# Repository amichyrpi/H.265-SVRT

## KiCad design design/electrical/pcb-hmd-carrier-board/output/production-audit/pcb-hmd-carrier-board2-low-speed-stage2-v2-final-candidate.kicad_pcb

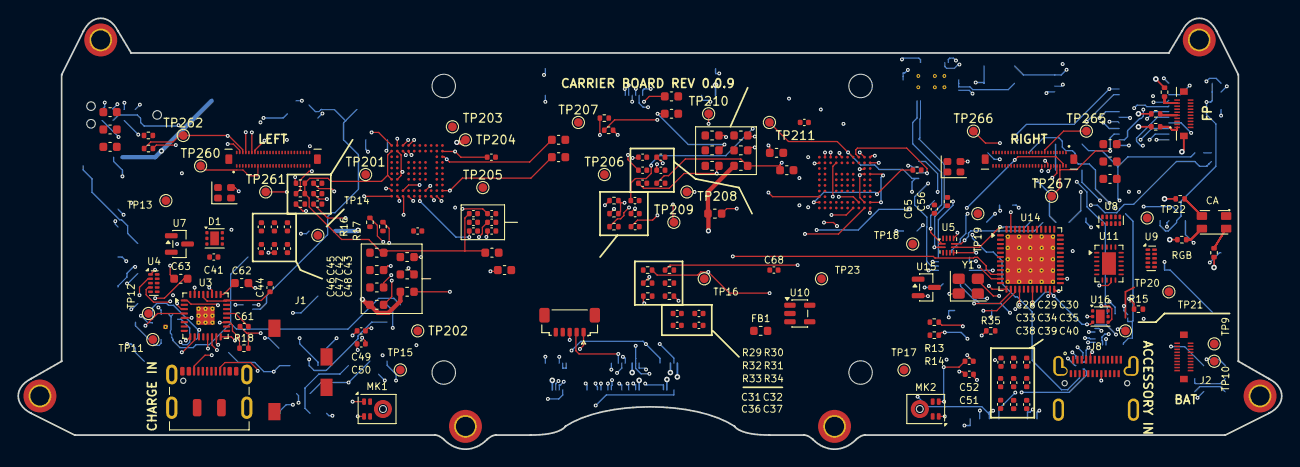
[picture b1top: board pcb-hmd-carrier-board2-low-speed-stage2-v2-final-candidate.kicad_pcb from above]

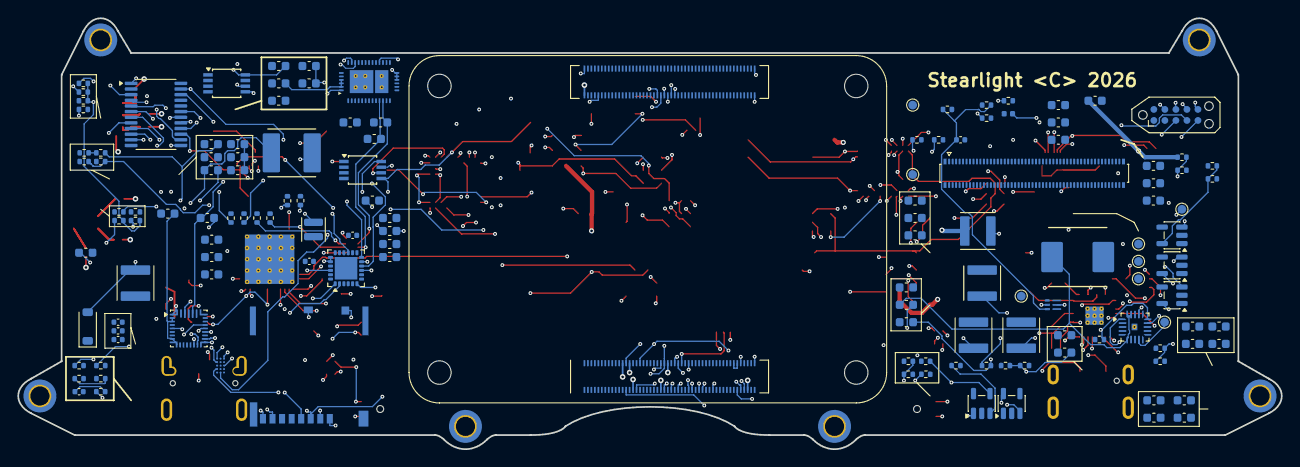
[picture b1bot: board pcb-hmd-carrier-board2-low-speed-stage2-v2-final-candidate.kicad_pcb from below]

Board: 6 copper layers, 145.5 x 49.6 mm, 312 parts (138 on the bottom side), 277 nets.

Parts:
C1, C2, C3, C4, C5, C9, C10, C11, C13, C14, C19, C20, C21, C22, C23: 10u; C_0603_1608Metric
C6, C12, C15, C24, C25: 100n; C_0603_1608Metric
C7, C8: 330p; C_0603_1608Metric
C16: 4u7; C_0603_1608Metric
C17, C18: 47n; C_0603_1608Metric
C26, C20120, C20121, C20220, C20221: 1u; C_0603_1608Metric
C27: 47p; C_0603_1608Metric
C28, C29, C30, C31, C32, C33, C34, C35, C36, C37, C43, C48, C290, C291, C2010, C2011, C2012, C2013, C2014, C2015, C2016, C2017, C2020, C2021, C2022, C2023, C2024, C2025, C2026, C2027, C20130, C20131, C20132, C20230, C20231, C20232: 100n; C_0402_1005Metric
C38, C44, C45, C46, C47: 10u; C_0402_1005Metric
C39, C40, C41, C42: 1u; C_0402_1005Metric
C49, C50, C51, C52: 1u C0G; C_0402_1005Metric
C55, C56: 100n PCIe AC; C_0402_1005Metric
C57, C58: 100u low-ESR; C_0603_1608Metric
C59, C60: 22u 25V; C_0603_1608Metric
C61: 100n JACK MIC; C_0402_1005Metric
C62: 47u HP LEFT; C_0603_1608Metric
C63: 47u HP RIGHT; C_0603_1608Metric
C64: 4.7u 10V; C_0603_1608Metric
C65, C66: 10u 6.3V; C_0603_1608Metric
C67: 120p C0G; C_0402_1005Metric
C68: 100n USB3 RESET; C_0402_1005Metric
C260, C265: 2.2uF; C_0603_1608Metric
C261, C262, C266, C267: 1uF 10V; C_0603_1608Metric
C270, C272, C273, C2031, C2041, C2051, C2061: 4.7uF 10V; C_0603_1608Metric
C271: 2.2uF 10V; C_0603_1608Metric
C274: 1uF; C_0603_1608Metric
C280: 68n COMP; C_0402_1005Metric
C281: 10uF 10V; C_0402_1005Metric
C282, C283: 10uF 16V; C_0402_1005Metric
C301: 10uF SD POWER (CM4 LITE ONLY); C_0603_1608Metric
C2032, C2042, C2052, C2062: 10uF 6.3V; C_0603_1608Metric
C20122, C20123, C20222, C20223: 2.2u; C_0603_1608Metric
D1: TVS2200DRVR; WSON-6-1EP_2x2mm_P0.65mm_EP1x1.6mm
D11: TJ-S3227 RGB COMMON ANODE C601674; TOGIALED_TJ-S3227SW1TCGLCCYRGB-A5
D201: DFLS160-7; D_SOD-123
FB1: 600R@100MHz ferrite; L_0603_1608Metric
FB2011, FB2012, FB2013, FB2014, FB2015, FB2016, FB2017, FB2021, FB2022, FB2023, FB2024, FB2025, FB2026, FB2027: 600R@100MHz; L_0603_1608Metric
H1, H2, H3, H4, H5, H6: MountingHole_2.2mm_M2_DIN965_Pad_TopBottom
J1: SJ-43514-SMT-TR; SameSky_SJ-43514-SMT-TR
J2: BM28 BATTERY FLEX 5A + NTC/ID; Hirose_BM28B0.6-20DS_2-0.35V
J6: TAG-CONNECT SERVICE PADS (NO FIT); Tag-Connect_TC2050-IDC-NL_2x05_P1.27mm_Vertical
J7: DF40C-100DP-0.4V(51) TRACKING; Hirose_DF40C-100DP-0.4V_2x50-1MP_P0.4mm
J8: DX07S024JJ2R1300 ACCESSORY; JAE_DX07S024JJ2R1300
J9: DX07S016JA1R1500 CHARGE/SERVICE; USB_C_Receptacle_JAE_DX07S016JA1R1500
J10: PROX SENSOR - SM05B-SURS-TF; JST_SUR_SM05B-SURS-TF_1x05-1MP_P0.80mm_Horizontal
J11: BM28B0.6-20DS/2-0.35V BUTTON FLEX; Hirose_BM28B0.6-20DS_2-0.35V_BUTTONS
J201: J_DISPLAY_LEFT 245863050104829+; Kyocera_245863050104829_50P_P0.35
J202: J_DISPLAY_RIGHT 245863050104829+; Kyocera_245863050104829_50P_P0.35
J301: Molex 503398-1892 (CM4 LITE ONLY); SDCARD_MOLEX_503398-1892
L1: 0.47uH XFL4015-471MEC; L_0402_1005Metric
L2: SRP7050TA-2R2M 2.2uH 10A; Bourns_SRP7050TA
L3: SRP5030CA-1R0M 1uH 9A; Bourns_SRP5030CA
L203, L204, L205, L206: 2.2uH; L_Abracon_ASPI-4030S
L207: 4.7uH 1.6A DFE252010; L_APV_ANR252010
L208: 10uH >=2.5A WLED; L_Abracon_ASPI-4030S
MK1, MK2: IM73A135V01; Infineon_PG-LLGA-5-2
Module1: CM4 2GB/16GB/Wireless; Raspberry-Pi-4-Compute-Module
R1: 220k; R_0402_1005Metric
R2: 30k; R_0402_1005Metric
R3: 5.23k ILIM; R_0402_1005Metric
R4: 137k ILIM; R_0402_1005Metric
R5, R6, R290, R291, R292, R293: 2.2k I2C; R_0402_1005Metric
R7, R8, R294, R295, R2011, R2021: 10k; R_0402_1005Metric
R9: 30.1k TS; R_0402_1005Metric
R10: 10k NTC; R_0402_1005Metric
R11: 100R BATP; R_0402_1005Metric
R12: 6.04k 2S; R_0402_1005Metric
R13, R14: 200k; R_0402_1005Metric
R15: ILIM 1.5A TBD; R_0402_1005Metric
R16, R17: I2C 2.2k; R_0402_1005Metric
R18: MICBIAS 2.7k; R_0402_1005Metric
R19: 75k 1V05 FB; R_0402_1005Metric
R20: 100k 1V05 FB; R_0402_1005Metric
R21: 100k 1V05 PG; R_0402_1005Metric
R22: 10k WIFI EN; R_0402_1005Metric
R23: 10k BT EN; R_0402_1005Metric
R24: 75k MODE; R_0402_1005Metric
R25: 51k MODE; R_0402_1005Metric
R26: 10k CLKREQ; R_0402_1005Metric
R27: 2.2k CHG SCL; R_0402_1005Metric
R28: 2.2k CHG SDA; R_0402_1005Metric
R29: 10k OCI PU; R_0402_1005Metric
R30: 1.6k RREF VERIFY; R_0402_1005Metric
R31: 10k RESET PU; R_0402_1005Metric
R32: 10k SPI CLK PD; R_0402_1005Metric
R33: 10k SPI CS PD; R_0402_1005Metric
R34: 10k SPI MISO PU; R_0402_1005Metric
R35: 10k SPI MOSI PD; R_0402_1005Metric
R73, R76, R77, R78: 1k; R_0402_1005Metric
R74, R75: 330R; R_0402_1005Metric
R260, R265: 100k RESET pulldown; R_0402_1005Metric
R261, R266: 0R DNP to BL_PWM; R_0402_1005Metric
R280: 37.4k 1% ISET=33.2mA; R_0402_1005Metric
R281: 49.9k 1% 1.25MHz; R_0402_1005Metric
R282: 147k 1% OVP; R_0402_1005Metric
R283: 20k 1% OVP; R_0402_1005Metric
R284: 3k COMP; R_0402_1005Metric
R301: 12k 1% SD_PWR_ON PU (CM4 LITE ONLY); R_0402_1005Metric
R302, R303: 0R SD DETECT OPTION; R_0402_1005Metric
R2010, R2020: 2.00k 1%; R_0402_1005Metric
R2012: 10k ADDR 0x0F; R_0402_1005Metric
R2022: 10k ADDR 0x1F; R_0402_1005Metric
R2031: 453k 1%; R_0402_1005Metric
R2032, R2042, R2051, R2052, R2062: 100k 1%; R_0402_1005Metric
R2041: 200k 1%; R_0402_1005Metric
R2061: 91k 1%; R_0402_1005Metric
TP1, TP9, TP10, TP11, TP12, TP13, TP14, TP15, TP16, TP17, TP18, TP19, TP20, TP21, TP22, TP23: CHG_STAT; TestPoint_Pad_D1.0mm
TP2: PGOOD_5V; TestPoint_Pad_D1.0mm
TP3: BAT_ID; TestPoint_Pad_D1.0mm
TP4: +5V_SYS; TestPoint_Pad_D1.0mm
TP5: +3V3; TestPoint_Pad_D1.0mm
TP6: +1V05_USB; TestPoint_Pad_D1.0mm
TP7: GND; TestPoint_Pad_D1.0mm
TP8: VBAT_SYS; TestPoint_Pad_D1.0mm
TP201: DISPLAY_5V; TestPoint_Pad_D1.0mm
TP202: DISPLAY_3V3; TestPoint_Pad_D1.0mm
TP203: DISPLAY_1V8; TestPoint_Pad_D1.0mm
TP204: DISPLAY_1V2; TestPoint_Pad_D1.0mm
TP205: DISPLAY_1V15; TestPoint_Pad_D1.0mm
TP206: LCD_VSP +5V5; TestPoint_Pad_D1.0mm
TP207: LCD_VSN -5V5; TestPoint_Pad_D1.0mm
TP208: BL_EN; TestPoint_Pad_D1.0mm
TP209: BL_PWM GPIO12; TestPoint_Pad_D1.0mm
TP210: I2C_SDA_1V8; TestPoint_Pad_D1.0mm
TP211: I2C_SCL_1V8; TestPoint_Pad_D1.0mm
TP260: L S1_TEST NC; TestPoint_Pad_D1.0mm
TP261: L TE; TestPoint_Pad_D1.0mm
TP262: L LEDPWM; TestPoint_Pad_D1.0mm
TP265: R S1_TEST NC; TestPoint_Pad_D1.0mm
TP266: R TE; TestPoint_Pad_D1.0mm
TP267: R LEDPWM; TestPoint_Pad_D1.0mm
U1: TPS62825DMQR; Texas_DMQ0006A_VSON-HR-6_1.5x1.5mm
U2: TPS568230RJER; Texas_RJE0020A_VQFN-20-1EP_3x3mm_P0.45mm_EP0.675x0.76mm_The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
U3: TLV320AIC3204IRHBR; Texas_RHB0032M_VQFN-32-1EP_5x5mm_P0.5mm_EP2.1x2.1mm_Thermal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
U4: TPD4E05U06DQAR; USON-10_2.5x1.0mm_P0.5mm
U5: TUSB320LAIRWBR; Texas_X2QFN-12_1.6x1.6mm_P0.4mm
U6: BQ25798RQMR; Texas_RQM0029A_VQFN-29_4x4mm_P0.4mm
U7: TPD2EUSB30DRTR; SOT-23
U8, U9: TPD4EUSB30DQAR; USON-10_2.5x1.0mm_P0.5mm
U10: TLV75528PDBVR; SOT-23-5
U11: HD3SS3212IRKSR; Texas_RVC0020A_WQFN-20-1EP_3x4mm_P0.5mm_EP1.6x2.6mm
U12: TPS25751DREFR; Texas_REF0038A_WQFN-38_6x4mm_DualPad
U13: CAT24C512WI-GT3; TSSOP-8_3x3mm_P0.65mm
U14: UPD720202K8-711-BAA-A; QFN-48-1EP_7x7mm_P0.5mm_EP5.7x5.7mm_ThermalVias
U15: TLV803EA30DBZR; SOT-23
U16: TPS2553-1DRVR; WSON-6-1EP_2x2mm_P0.65mm_EP1x1.6mm
U201, U202: TC358870XBG(NOK) C3008712; Toshiba_P-VFBGA80_7x7mm_P0.65
U203, U204, U205, U206: TLV62569DBVR; SOT-23-5
U207: TPS65132B5YFFR; TI_DSBGA15_YFF_2.108x1.514mm_P0.4
U208: MP3387AGRT-P; TQFN-24-1EP_4x4mm_P0.5mm_EP2.6x2.6mm
U209: PCA9306DCTR C123752; TSSOP-8_3x3mm_P0.65mm
U210: TCA9539PWR 1V8 DISPLAY GPIO; TSSOP-24_4.4x7.8mm_P0.65mm
U301: RT9742GGJ5 SD POWER (CM4 LITE ONLY); SOT-23-5
Y1: 24MHz; Crystal_SMD_3225-4Pin_3.2x2.5mm
Y201, Y202: SIT8008ACE73-18E-48.000000E; Oscillator_SMD_SiT_PQFN-4Pin_2.0x1.6mm

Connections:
+1V05_USB: C28.1, C29.1, C30.1, C31.1, C32.1, C33.1, C39.1, C65.1, C66.1, C67.1, L1.2, R19.1, TP6.1, U14.6, U14.9, U14.21, U14.30, U14.33, U14.39, U14.42
+1V8: Module1.88, Module1.90
+2V8_MIC: C42.1, MK1.2, MK2.2, U10.5
+3V3: C3.1, C34.1, C35.1, C36.1, C37.1, C38.1, C40.1, C43.1, C64.1, C68.1, D11.1, FB1.1, J6.1, J10.4, Module1.78, Module1.84, Module1.86, R8.1, R13.1, R14.1, R16.1, R17.1, R21.1, R22.1, R23.1, R26.1, R29.1, R31.1, R34.1, R290.2, R291.2, R301.1, TP5.1, U1.1, U1.6, U3.6, U3.30, U5.3, U5.12, U11.6, U12.38, U14.3, U14.12, U14.22, U14.25, U14.34, U14.43, U15.3, U209.2, U301.5
+3V3_AUDIO: C41.1, C45.1, C48.1, FB1.2, U3.26, U10.1, U10.3
+5V_SYS: C57.1, C58.1, C270.1, C281.1, C2031.1, C2041.1, C2051.1, C2061.1, L2.2, L207.1, L208.1, Module1.77, Module1.79, Module1.81, Module1.83, Module1.85, Module1.87, R1.1, TP4.1, TP201.1, U12.34, U12.35, U16.6, U203.1, U203.4, U204.1, U204.4, U205.1, U205.4, U206.1, U206.4, U207.C1, U208.23, U208.24
AUDIO_1V8_LDO: C44.1, U3.24, U3.29
AUDIO_MCLK: Module1.54, U3.1
AUDIO_REF: C46.1, U3.18
AUDIO_RESET_N: Module1.34, U3.31
BAT+: C24.1, R11.2, U6.22, U6.23
BATP: R11.1, U6.18
BIAS_FLY1: C271.1, U207.C3
BIAS_FLY2: C271.2, U207.A3
BIAS_REG: C274.1, U207.D3, U207.E2
BIAS_SW: L207.2, U207.D1
BL_EN: TP208.1, U208.1, U210.13
BL_PWM: Module1.31, R261.2, R266.2, TP209.1, U208.6
BST1: C17.1, U6.4
BST2: C18.1, U6.19
BST_5V: C25.1, U2.1
BT_ENABLE_N: Module1.91, R23.2
CC1: C7.1, J8.A5, J9.A5, U5.1, U12.28
CC2: C8.1, J8.B5, J9.B5, U5.2, U12.29
CHG_IRQ_N: R8.2, U6.21, U12.18
CHG_SCL: R27.2, U6.14, U12.17
CHG_SDA: R28.2, U6.15, U12.16
CHG_STAT: TP1.1, U6.1
CM4_EXT_RESET_N: J6.8, Module1.100
DISPLAY_1V2: C2052.1, FB2016.1, FB2017.1, FB2026.1, FB2027.1, L205.2, R2051.1, TP204.1
DISPLAY_1V8: C260.1, C265.1, C290.1, C291.1, C2010.1, C2020.1, C2042.1, FB2013.1, FB2023.1, J201.2, J201.4, J202.2, J202.4, L204.2, R292.2, R293.2, R294.2, R295.2, R2022.2, R2041.1, TP203.1, U209.3, U209.4, U210.24, Y201.1, Y201.4, Y202.1, Y202.4
DISPLAY_1V15: C2062.1, FB2014.1, FB2015.1, FB2024.1, FB2025.1, L206.2, R2061.1, TP205.1
DISPLAY_3V3: C2032.1, FB2011.1, FB2012.1, FB2021.1, FB2022.1, L203.2, R2031.1, TP202.1
DISPLAY_GPIO_INT_N: R295.1, U210.1
DISPLAY_GPIO_RESETN: R294.1, U210.3
DISPLAY_I2C_SCL_1V8: R293.1, TP211.1, U201.K4, U202.K4, U207.B2, U209.5, U210.22
DISPLAY_I2C_SDA_1V8: R292.1, TP210.1, U201.K3, U202.K3, U207.C2, U209.6, U210.23
EMMC_BOOT_N: J6.7, Module1.93
FB_5V: C27.1, R1.2, R2.1, U2.14
GND: C1.2, C2.2, C3.2, C4.2, C5.2, C6.2, C7.2, C8.2, C9.2, C10.2, C11.2, C12.2, C13.2, C14.2, C15.2, C16.2, C19.2, C20.2, C21.2, C22.2, C23.2, C24.2, C26.2, C27.2, C28.2, C29.2, C30.2, C31.2, C32.2, C33.2, C34.2, C35.2, C36.2, C37.2, C38.2, C39.2, C40.2, C41.2, C42.2, C43.2, C44.2, C45.2, C46.2, C47.2, C48.2, C57.2, C58.2, C59.2, C60.2, C64.2, C65.2, C66.2, C68.2, C260.2, C261.2, C262.2, C265.2, C266.2, C267.2, C270.2, C272.2, C273.2, C274.2, C280.2, C281.2, C282.2, C283.2, C290.2, C291.2, C301.2, C2010.2, C2011.2, C2012.2, C2013.2, C2014.2, C2015.2, C2016.2, C2017.2, C2020.2, C2021.2, C2022.2, C2023.2, C2024.2, C2025.2, C2026.2, C2027.2, C2031.2, C2032.2, C2041.2, C2042.2, C2051.2, C2052.2, C2061.2, C2062.2, C20120.2, C20121.2, C20122.2, C20123.2, C20130.2, C20131.2, C20132.2, C20220.2, C20221.2, C20222.2, C20223.2, C20230.2, C20231.2, C20232.2, D1.1, D1.2, D1.3, D1.7, J6.2, J6.10, J8.A1, J8.A12, J8.B1, J8.B12, J8.SH, J9.A1, J9.A12, J9.B1, J9.B12, J10.5, J11.21, J201.1, J201.5, J201.6, J201.9, J201.10, J201.15, J201.16, J201.21, J201.22, J201.27, J201.28, J201.33, J201.34, J201.39, J201.40, J201.43, J201.46, J201.50, J202.1, J202.5, J202.6, J202.9, J202.10, J202.15, J202.16, J202.21, J202.22, J202.27, J202.28, J202.33, J202.34, J202.39, J202.40, J202.43, J202.46, J202.50, J301.6, J301.11, MK1.4, MK1.5, MK2.4, MK2.5, Module1.1, Module1.2, Module1.7, Module1.8, Module1.13, Module1.14, Module1.22, Module1.23, Module1.32, Module1.33, Module1.42, Module1.43, Module1.52, Module1.53, Module1.59, Module1.60, Module1.65, Module1.66, Module1.71, Module1.74, Module1.98, Module1.101, Module1.107, Module1.108, Module1.113, Module1.114, Module1.119, Module1.120, Module1.125, Module1.126, Module1.131, Module1.132, Module1.137, Module1.138, Module1.144, Module1.150, Module1.155, Module1.156, Module1.161, Module1.162, Module1.167, Module1.168, Module1.173, Module1.174, Module1.179, Module1.180, Module1.185, Module1.186, Module1.191, Module1.192, Module1.197, Module1.198, R2.2, R4.2, R9.2, R10.2, R12.2, R15.2, R20.2, R25.2, R30.2, R32.2, R33.2, R35.2, R260.2, R265.2, R280.2, R281.2, R283.2, R302.2, R303.2, R2012.2, R2032.2, R2042.2, R2052.2, R2062.2, TP7.1, U1.4, U2.7, U2.8, U2.13, U2.18, U2.21, U3.7, U3.12, U3.17, U3.28, U4.3, U4.5, U4.8, U5.5, U5.10, U5.11, U6.10, U6.11, U6.12, U6.13, U6.27, U7.3, U8.3, U8.8, U9.3, U9.8, U10.2, U11.2, U11.5, U11.11, U11.20, U12.11, U12.12, U12.14, U12.31, U12.39, U13.1, U13.2, U13.3, U13.4, U13.7, U14.27, U14.49, U15.1, U16.5, U16.7, U201.A10, U201.C9, U201.D4, U201.D5, U201.D6, U201.D7, U201.E4, U201.E5, U201.E6, U201.E7, U201.F4, U201.F5, U201.F6, U201.F7, U201.G4, U201.G5, U201.G6, U201.G7, U201.H1, U201.K10, U202.A10, U202.C9, U202.D4, U202.D5, U202.D6, U202.D7, U202.E4, U202.E5, U202.E6, U202.E7, U202.F4, U202.F5, U202.F6, U202.F7, U202.G4, U202.G5, U202.G6, U202.G7, U202.H1, U202.K10, U203.2, U204.2, U205.2, U206.2, U207.B3, U207.D2, U207.E1, U208.3, U208.4, U208.5, U208.7, U208.8, U208.17, U208.18, U208.21, U208.25, U209.1, U210.2, U210.12, U210.21, U301.2, Y1.2, Y1.4, Y201.2, Y202.2
HDMI_L_CEC: Module1.151, U201.A2
HDMI_L_CLK_N: Module1.190, U201.C2
HDMI_L_CLK_P: Module1.188, U201.C1
HDMI_L_D0_N: Module1.184, U201.D2
HDMI_L_D0_P: Module1.182, U201.D1
HDMI_L_D1_N: Module1.178, U201.E2
HDMI_L_D1_P: Module1.176, U201.E1
HDMI_L_D2_N: Module1.172, U201.F2
HDMI_L_D2_P: Module1.170, U201.F1
HDMI_L_DDC_SCL: Module1.200, U201.A3
HDMI_L_DDC_SDA: Module1.199, U201.B3
HDMI_L_HPD: Module1.153, U201.B4
HDMI_R_CEC: Module1.149, U202.A2
HDMI_R_CLK_N: Module1.166, U202.C2
HDMI_R_CLK_P: Module1.164, U202.C1
HDMI_R_D0_N: Module1.160, U202.D2
HDMI_R_D0_P: Module1.158, U202.D1
HDMI_R_D1_N: Module1.154, U202.E2
HDMI_R_D1_P: Module1.152, U202.E1
HDMI_R_D2_N: Module1.148, U202.F2
HDMI_R_D2_P: Module1.146, U202.F1
HDMI_R_DDC_SCL: Module1.147, U202.A3
HDMI_R_DDC_SDA: Module1.145, U202.B3
HDMI_R_HPD: Module1.143, U202.B4
HP_L: C62.2, U4.1
HP_L_CODEC: C62.1, U3.25
HP_R: C63.2, U4.2
HP_R_CODEC: C63.1, U3.27
I2C_SCL: J6.4, J10.3, Module1.56, R16.2, R291.1, U3.9, U5.8, U209.8
I2C_SDA: J6.3, J10.2, Module1.58, R17.2, R290.1, U3.10, U5.7, U209.7
I2Ct_SCL: R6.2, U12.9, U13.6
I2Ct_SDA: R5.2, U12.8, U13.5
I2S_BCLK: Module1.49, U3.2
I2S_DIN: Module1.27, U3.5
I2S_DOUT: Module1.25, U3.4
I2S_LRCLK: Module1.26, U3.3
ILIM_HIZ: R3.2, R4.1, U6.17
JACK_MIC: C61.1, R18.2, U4.4
JACK_MIC_CODEC: C61.2, U3.21
LCD_BIAS_ENN: U207.A1, U210.19
LCD_BIAS_ENP: U207.B1, U210.18
LCD_VSN: C262.1, C267.1, C273.1, J201.7, J202.7, TP207.1, U207.A2
LCD_VSP: C261.1, C266.1, C272.1, J201.3, J202.3, TP206.1, U207.E3
LDO_1V5: C2.1, U12.2, U12.3, U12.4
LDO_3V3: C1.1, R5.1, R6.1, R7.1, R27.1, R28.1, U12.1, U13.8
LED_BLUE_GPIO16_N: Module1.29, R75.1
LED_BLUE_K: D11.4, R75.2
LED_BOOST: C282.1, C283.1, D201.1, J201.41, J202.41, R282.1
LED_GREEN_GPIO13_N: Module1.28, R74.1
LED_GREEN_K: D11.3, R74.2
LED_RED_K: D11.2, R73.2
L_1V2_MIPI0: C2016.1, C20123.1, FB2016.2, U201.J10
L_1V2_MIPI1: C2017.1, FB2017.2, U201.B10
L_1V8_IO: C2013.1, C20121.1, FB2013.2, U201.J7
L_1V15_CORE: C2015.1, C20122.1, FB2015.2, U201.C10, U201.K6
L_1V15_HDMI: C2014.1, FB2014.2, U201.B2, U201.G2
L_3V3_HDMI: C2011.1, C20120.1, FB2011.2, R2010.2, R2011.2, U201.B1, U201.G1
L_3V3_IO: C2012.1, FB2012.2, U201.H2
L_BIASDA: C20130.1, U201.J1
L_BRIDGE_INT: R2012.1, U201.J3, U210.6
L_BRIDGE_RESETN: U201.K8, U210.4
L_DSIA_CLK_N: J201.18, U201.F9
L_DSIA_CLK_P: J201.20, U201.F10
L_DSIA_D0_N: J201.11, U201.H9
L_DSIA_D0_P: J201.13, U201.H10
L_DSIA_D1_N: J201.17, U201.G9
L_DSIA_D1_P: J201.19, U201.G10
L_DSIA_D2_N: J201.24, U201.E9
L_DSIA_D2_P: J201.26, U201.E10
L_DSIA_D3_N: J201.12, U201.D9
L_DSIA_D3_P: J201.14, U201.D10
L_DSIB_CLK_N: J201.31, U201.B7
L_DSIB_CLK_P: J201.29, U201.A7
L_DSIB_D0_N: J201.38, U201.B9
L_DSIB_D0_P: J201.36, U201.A9
L_DSIB_D1_N: J201.32, U201.B8
L_DSIB_D1_P: J201.30, U201.A8
L_DSIB_D2_N: J201.25, U201.B6
L_DSIB_D2_P: J201.23, U201.A6
L_DSIB_D3_N: J201.37, U201.B5
L_DSIB_D3_P: J201.35, U201.A5
L_HPDI: R2011.1, U201.A4, U210.16
L_LCD_LEDPWM: J201.48, R261.1, TP262.1, U210.14
L_LCD_RESET: J201.42, R260.1, U210.8
L_LCD_TE: J201.44, TP261.1, U210.10
L_LED1_N: J201.45, U208.15
L_LED2_N: J201.47, U208.14
L_LED3_N: J201.49, U208.13
L_PCKIN: C20131.1, U201.K1
L_PFIL: C20132.1, U201.K2
L_REFCLK: U201.K9, Y201.3
L_REXT: R2010.1, U201.A1
L_S1_TEST: J201.8, TP260.1
MICBIAS: C47.1, R18.1, U3.19
MIC_L_N: C50.2, U3.16
MIC_L_P: C49.2, U3.15
MIC_L_RAW_N: C50.1, MK1.3
MIC_L_RAW_P: C49.1, MK1.1
MIC_R_N: C52.2, U3.13
MIC_R_P: C51.2, U3.14
MIC_R_RAW_N: C52.1, MK2.3
MIC_R_RAW_P: C51.1, MK2.1
MODE_5V: R24.2, R25.1, U2.15
PCIE_CLKREQ_N: Module1.102, R26.2, U14.10
PCIE_CLK_N: Module1.112, U14.2
PCIE_CLK_P: Module1.110, U14.1
PCIE_RST_N: Module1.109, U14.47
PCIE_RX_N: C56.2, Module1.124
PCIE_RX_P: C55.2, Module1.122
PCIE_RX_USB3_N: C56.1, U14.5
PCIE_RX_USB3_P: C55.1, U14.4
PCIE_TX_N: Module1.118, U14.8
PCIE_TX_P: Module1.116, U14.7
PD_IRQ_N: R7.2, U12.10
PGOOD_5V: TP2.1, U2.9
PMID: C13.1, C14.1, C15.1, U6.29
PPHV: C4.1, C5.1, C6.1, U6.2, U6.3, U6.8, U6.9, U12.20, U12.21, U12.22
PROG: R12.1, U6.20
PROX_INT: J10.1, Module1.47
PWR_KEY_GPIO26_N: Module1.24, R76.1
PWR_KEY_N: J11.1, R76.2
REGN: C16.1, R3.1, U6.5
REG_1V2_FB: R2051.2, R2052.1, U205.5
REG_1V2_SW: L205.1, U205.3
REG_1V8_FB: R2041.2, R2042.1, U204.5
REG_1V8_SW: L204.1, U204.3
REG_1V15_FB: R2061.2, R2062.1, U206.5
REG_1V15_SW: L206.1, U206.3
REG_3V3_FB: R2031.2, R2032.1, U203.5
REG_3V3_SW: L203.1, U203.3
RUN_PG: J6.9, Module1.92
R_1V2_MIPI0: C2026.1, C20223.1, FB2026.2, U202.J10
R_1V2_MIPI1: C2027.1, FB2027.2, U202.B10
R_1V8_IO: C2023.1, C20221.1, FB2023.2, U202.J7
R_1V15_CORE: C2025.1, C20222.1, FB2025.2, U202.C10, U202.K6
R_1V15_HDMI: C2024.1, FB2024.2, U202.B2, U202.G2
R_3V3_HDMI: C2021.1, C20220.1, FB2021.2, R2020.2, R2021.2, U202.B1, U202.G1
R_3V3_IO: C2022.1, FB2022.2, U202.H2
R_BIASDA: C20230.1, U202.J1
R_BRIDGE_INT: R2022.1, U202.J3, U210.7
R_BRIDGE_RESETN: U202.K8, U210.5
R_DSIA_CLK_N: J202.18, U202.F9
R_DSIA_CLK_P: J202.20, U202.F10
R_DSIA_D0_N: J202.11, U202.H9
R_DSIA_D0_P: J202.13, U202.H10
R_DSIA_D1_N: J202.17, U202.G9
R_DSIA_D1_P: J202.19, U202.G10
R_DSIA_D2_N: J202.24, U202.E9
R_DSIA_D2_P: J202.26, U202.E10
R_DSIA_D3_N: J202.12, U202.D9
R_DSIA_D3_P: J202.14, U202.D10
R_DSIB_CLK_N: J202.31, U202.B7
R_DSIB_CLK_P: J202.29, U202.A7
R_DSIB_D0_N: J202.38, U202.B9
R_DSIB_D0_P: J202.36, U202.A9
R_DSIB_D1_N: J202.32, U202.B8
R_DSIB_D1_P: J202.30, U202.A8
R_DSIB_D2_N: J202.25, U202.B6
R_DSIB_D2_P: J202.23, U202.A6
R_DSIB_D3_N: J202.37, U202.B5
R_DSIB_D3_P: J202.35, U202.A5
R_HPDI: R2021.1, U202.A4, U210.17
R_LCD_LEDPWM: J202.48, R266.1, TP267.1, U210.15
R_LCD_RESET: J202.42, R265.1, U210.9
R_LCD_TE: J202.44, TP266.1, U210.11
R_LED1_N: J202.45, U208.12
R_LED2_N: J202.47, U208.10
R_LED3_N: J202.49, U208.9
R_PCKIN: C20231.1, U202.K1
R_PFIL: C20232.1, U202.K2
R_REFCLK: U202.K9, Y202.3
R_REXT: R2020.1, U202.A1
R_S1_TEST: J202.8, TP265.1
SD_CLK: J301.5, Module1.57
SD_CMD: J301.3, Module1.62
SD_DAT0: J301.7, Module1.63
SD_DAT1: J301.8, Module1.67
SD_DAT2: J301.1, Module1.69
SD_DAT3: J301.2, Module1.61
SD_DETECT_A: J301.9, R302.1
SD_DETECT_B: J301.10, R303.1, U301.3
SD_PWR: C301.1, J301.4, U301.1
SD_PWR_ON: Module1.75, R301.2, U301.4
SPI_CLK: R32.1, U14.15
SPI_CS_N: R33.1, U14.14
SPI_MISO: R34.2, U14.13
SPI_MOSI: R35.1, U14.16
SW1: C17.2, L3.1, U6.28
SW2: C18.2, L3.2, U6.26
SW_5V: C25.2, L2.1, U2.6, U2.19, U2.20
TS: R9.1, R10.1, U6.16
TYPEC_ATTACHED_N: R14.2, U5.9, U16.4
TYPEC_FLIP: Module1.48, U11.9
TYPEC_INT_N: Module1.46, R13.2, U5.6
UART_RX: J6.6, Module1.51
UART_TX: J6.5, Module1.55
USB1V05_FB: C67.2, R19.2, R20.1, U1.3
USB1V05_PG: R21.2, U1.2
USB1V05_SW: L1.1, U1.5
USB2_HOST_DM: J8.A7, J8.B7, U7.2, U14.36
USB2_HOST_DP: J8.A6, J8.B6, U7.1, U14.35
USB2_SERVICE_DM: J9.A7, J9.B7, Module1.103, U12.27
USB2_SERVICE_DP: J9.A6, J9.B6, Module1.105, U12.26
USB3_POR_N: R31.2, U14.11, U15.2
USB3_RREF: R30.1, U14.26
USB3_RX_N: U11.8, U14.32
USB3_RX_P: U11.7, U14.31
USB3_TX_N: U11.4, U14.29
USB3_TX_P: U11.3, U14.28
USB3_XT1: U14.24, Y1.1
USB3_XT2: U14.23, Y1.3
USB_C_RX1_N: J8.B10, U8.5, U11.16
USB_C_RX1_P: J8.B11, U8.4, U11.17
USB_C_RX2_N: J8.A10, U9.5, U11.12
USB_C_RX2_P: J8.A11, U9.4, U11.13
USB_C_TX1_N: J8.A3, U8.2, U11.18
USB_C_TX1_P: J8.A2, U8.1, U11.19
USB_C_TX2_N: J8.B3, U9.2, U11.14
USB_C_TX2_P: J8.B2, U9.1, U11.15
USB_ILIM: R15.1, U16.2
USB_OC_N: R29.2, U14.19, U16.3
VBAT_SYS: C19.1, C20.1, C21.1, C22.1, C23.1, C59.1, C60.1, TP8.1, U2.2, U2.3, U2.4, U2.5, U2.12, U6.25
VBUS_CHARGE: C9.1, C10.1, C11.1, C12.1, D1.4, D1.5, D1.6, J9.A4, J9.A9, J9.B4, J9.B9, U12.23, U12.24, U12.25, U12.32, U12.33
VBUS_USB_HOST: J8.A4, J8.A9, J8.B4, J8.B9, U16.1
VCC_5V: C26.1, R24.1, U2.17
VOL_DOWN_GPIO17_N: Module1.50, R78.1
VOL_DOWN_N: J11.17, R78.2
VOL_UP_GPIO24_N: Module1.45, R77.1
VOL_UP_N: J11.9, R77.2
WIFI_ENABLE_N: Module1.89, R22.2
WLED_COMP: R284.1, U208.22
WLED_COMP_RC: C280.1, R284.2
WLED_FREQ: R281.1, U208.2
WLED_ISET: R280.1, U208.11
WLED_OVP: R282.2, R283.1, U208.16
WLED_SW: D201.2, L208.2, U208.19, U208.20
nPI_LED_PWR: Module1.95, R73.1

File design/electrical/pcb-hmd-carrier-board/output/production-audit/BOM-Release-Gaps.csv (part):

Reference,Value,Missing_release_fields
C1,10u,Manufacturer; MPN; Supplier part number
C10,10u,Manufacturer; MPN; Supplier part number
C11,10u,Manufacturer; MPN; Supplier part number
C12,100n,Manufacturer; MPN; Supplier part number
C13,10u,Manufacturer; MPN; Supplier part number
C14,10u,Manufacturer; MPN; Supplier part number
C15,100n,Manufacturer; MPN; Supplier part number
C16,4u7,Manufacturer; MPN; Supplier part number
C17,47n,Manufacturer; MPN; Supplier part number
C18,47n,Manufacturer; MPN; Supplier part number
C19,10u,Manufacturer; MPN; Supplier part number
C2,10u,Manufacturer; MPN; Supplier part number
C20,10u,Manufacturer; MPN; Supplier part number
C2010,100n,Manufacturer; MPN; Supplier part number
C2011,100n,Manufacturer; MPN; Supplier part number
C2012,100n,Manufacturer; MPN; Supplier part number
C20120,1u,Manufacturer; MPN; Supplier part number
C20121,1u,Manufacturer; MPN; Supplier part number
C20122,2.2u,Manufacturer; MPN; Supplier part number
C20123,2.2u,Manufacturer; MPN; Supplier part number
C2013,100n,Manufacturer; MPN; Supplier part number
C20130,100n,Manufacturer; MPN; Supplier part number
C20131,100n,Manufacturer; MPN; Supplier part number
C20132,100n,Manufacturer; MPN; Supplier part number
C2014,100n,Manufacturer; MPN; Supplier part number
C2015,100n,Manufacturer; MPN; Supplier part number
C2016,100n,Manufacturer; MPN; Supplier part number
C2017,100n,Manufacturer; MPN; Supplier part number
C2020,100n,Manufacturer; MPN; Supplier part number
C2021,100n,Manufacturer; MPN; Supplier part number
C2022,100n,Manufacturer; MPN; Supplier part number
C20220,1u,Manufacturer; MPN; Supplier part number
C20221,1u,Manufacturer; MPN; Supplier part number
C20222,2.2u,Manufacturer; MPN; Supplier part number
C20223,2.2u,Manufacturer; MPN; Supplier part number
C2023,100n,Manufacturer; MPN; Supplier part number
C20230,100n,Manufacturer; MPN; Supplier part number
C20231,100n,Manufacturer; MPN; Supplier part number
C20232,100n,Manufacturer; MPN; Supplier part number
C2024,100n,Manufacturer; MPN; Supplier part number
C2025,100n,Manufacturer; MPN; Supplier part number
C2026,100n,Manufacturer; MPN; Supplier part number
C2027,100n,Manufacturer; MPN; Supplier part number
C2031,4.7uF 10V,Manufacturer; MPN; Supplier part number
C2032,10uF 6.3V,Manufacturer; MPN; Supplier part number
C2041,4.7uF 10V,Manufacturer; MPN; Supplier part number
C2042,10uF 6.3V,Manufacturer; MPN; Supplier part number
C2051,4.7uF 10V,Manufacturer; MPN; Supplier part number
C2052,10uF 6.3V,Manufacturer; MPN; Supplier part number
C2061,4.7uF 10V,Manufacturer; MPN; Supplier part number
C2062,10uF 6.3V,Manufacturer; MPN; Supplier part number
C21,10u,Manufacturer; MPN; Supplier part number
C22,10u,Manufacturer; MPN; Supplier part number
C23,10u,Manufacturer; MPN; Supplier part number
C24,100n,Manufacturer; MPN; Supplier part number
C25,100n,Manufacturer; MPN; Supplier part number
C26,1u,Manufacturer; MPN; Supplier part number
C260,2.2uF,Manufacturer; MPN; Supplier part number
C261,1uF 10V,Manufacturer; MPN; Supplier part number
C262,1uF 10V,Manufacturer; MPN; Supplier part number
C265,2.2uF,Manufacturer; MPN; Supplier part number
C266,1uF 10V,Manufacturer; MPN; Supplier part number
C267,1uF 10V,Manufacturer; MPN; Supplier part number
C27,47p,Manufacturer; MPN; Supplier part number
C270,4.7uF 10V,Manufacturer; MPN; Supplier part number
C271,2.2uF 10V,Manufacturer; MPN; Supplier part number
C272,4.7uF 10V,Manufacturer; MPN; Supplier part number
C273,4.7uF 10V,Manufacturer; MPN; Supplier part number
C274,1uF,Manufacturer; MPN; Supplier part number
C28,100n,Manufacturer; MPN; Supplier part number
C280,68n COMP,Manufacturer; MPN; Supplier part number
C281,10uF 10V,Manufacturer; MPN; Supplier part number
C282,10uF 16V,Manufacturer; MPN; Supplier part number
C283,10uF 16V,Manufacturer; MPN; Supplier part number
C29,100n,Manufacturer; MPN; Supplier part number
C290,100n,Manufacturer; MPN; Supplier part number
C291,100n,Manufacturer; MPN; Supplier part number
C3,10u,Manufacturer; MPN; Supplier part number
C30,100n,Manufacturer; MPN; Supplier part number
C301,10uF SD POWER (CM4 LITE ONLY),Manufacturer; MPN; Supplier part number
C31,100n,Manufacturer; MPN; Supplier part number
C32,100n,Manufacturer; MPN; Supplier part number
C33,100n,Manufacturer; MPN; Supplier part number
C34,100n,Manufacturer; MPN; Supplier part number
C35,100n,Manufacturer; MPN; Supplier part number
C36,100n,Manufacturer; MPN; Supplier part number
C37,100n,Manufacturer; MPN; Supplier part number
C38,10u,Manufacturer; MPN; Supplier part number
C39,1u,Manufacturer; MPN; Supplier part number
C4,10u,Manufacturer; MPN; Supplier part number
C40,1u,Manufacturer; MPN; Supplier part number
C41,1u,Manufacturer; MPN; Supplier part number
C42,1u,Manufacturer; MPN; Supplier part number
C43,100n,Manufacturer; MPN; Supplier part number
C44,10u,Manufacturer; MPN; Supplier part number
C45,10u,Manufacturer; MPN; Supplier part number
C46,10u,Manufacturer; MPN; Supplier part number
C47,10u,Manufacturer; MPN; Supplier part number
C48,100n,Manufacturer; MPN; Supplier part number
C49,1u C0G,Manufacturer; MPN; Supplier part number
C5,10u,Manufacturer; MPN; Supplier part number
C50,1u C0G,Manufacturer; MPN; Supplier part number
C51,1u C0G,Manufacturer; MPN; Supplier part number
C52,1u C0G,Manufacturer; MPN; Supplier part number
C55,100n PCIe AC,Manufacturer; MPN; Supplier part number
C56,100n PCIe AC,Manufacturer; MPN; Supplier part number
C57,100u low-ESR,Manufacturer; MPN; Supplier part number
C58,100u low-ESR,Manufacturer; MPN; Supplier part number
C59,22u 25V,Manufacturer; MPN; Supplier part number
C6,100n,Manufacturer; MPN; Supplier part number
C60,22u 25V,Manufacturer; MPN; Supplier part number
C61,100n JACK MIC,Manufacturer; MPN; Supplier part number
C62,47u HP LEFT,Manufacturer; MPN; Supplier part number
C63,47u HP RIGHT,Manufacturer; MPN; Supplier part number
C64,4.7u 10V,Manufacturer; MPN; Supplier part number
C65,10u 6.3V,Manufacturer; MPN; Supplier part number
C66,10u 6.3V,Manufacturer; MPN; Supplier part number
C67,120p C0G,Manufacturer; MPN; Supplier part number
C68,100n USB3 RESET,Manufacturer; MPN; Supplier part number
C7,330p,Manufacturer; MPN; Supplier part number
C8,330p,Manufacturer; MPN; Supplier part number
C9,10u,Manufacturer; MPN; Supplier part number
D1,TVS2200DRVR,Manufacturer; MPN; Supplier part number
D11,TJ-S3227 RGB COMMON ANODE C601674,Manufacturer; MPN; Supplier part number
D201,DFLS160-7,Manufacturer; MPN; Supplier part number
FB1,600R@100MHz ferrite,Manufacturer; MPN; Supplier part number
FB2011,600R@100MHz,Manufacturer; MPN; Supplier part number
FB2012,600R@100MHz,Manufacturer; MPN; Supplier part number
FB2013,600R@100MHz,Manufacturer; MPN; Supplier part number
FB2014,600R@100MHz,Manufacturer; MPN; Supplier part number
FB2015,600R@100MHz,Manufacturer; MPN; Supplier part number
FB2016,600R@100MHz,Manufacturer; MPN; Supplier part number
FB2017,600R@100MHz,Manufacturer; MPN; Supplier part number
FB2021,600R@100MHz,Manufacturer; MPN; Supplier part number
FB2022,600R@100MHz,Manufacturer; MPN; Supplier part number
FB2023,600R@100MHz,Manufacturer; MPN; Supplier part number
FB2024,600R@100MHz,Manufacturer; MPN; Supplier part number
FB2025,600R@100MHz,Manufacturer; MPN; Supplier part number
FB2026,600R@100MHz,Manufacturer; MPN; Supplier part number
FB2027,600R@100MHz,Manufacturer; MPN; Supplier part number
J1,SJ-43514-SMT-TR,Manufacturer; MPN; Supplier part number
J10,PROX SENSOR - SM05B-SURS-TF,Manufacturer; MPN; Supplier part number
J11,BM28B0.6-20DS/2-0.35V BUTTON FLEX,Manufacturer; MPN; Supplier part number
J2,BM28 BATTERY FLEX 5A + NTC/ID,Manufacturer; MPN; Supplier part number
J201,J_DISPLAY_LEFT 245863050104829+,Manufacturer; MPN; Supplier part number
J202,J_DISPLAY_RIGHT 245863050104829+,Manufacturer; MPN; Supplier part number
J301,Molex 503398-1892 (CM4 LITE ONLY),Manufacturer; MPN; Supplier part number
J7,DF40C-100DP-0.4V(51) TRACKING,Manufacturer; MPN; Supplier part number
J8,DX07S024JJ2R1300 ACCESSORY,Manufacturer; MPN
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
